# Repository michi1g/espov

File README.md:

# MiniPOV WiFi

ESP8266-Nachbau des [Adafruit MiniPOV3](https://learn.adafruit.com/minipov3) mit WiFi-Web-Editor, **2×AA-Betrieb** und optionalem **USB-C**.

## Features

- 8-LED-POV-Display (Persistence of Vision)
- **2× AA** wie beim Original (+ Boost-Wandler auf 5 V)
- **USB-C** optional auf der Platine (Laden ohne Micro-USB-Kabel am Wemos)
- WiFi **nur bei Bedarf** – FLASH-Taste, Auto-Timeout nach 3 Min.
- Web-Editor: Pixel, Text, Bild-Upload, Vorschau

## Bedienung

### POV anzeigen (Standard)

1. Einschalten (Batterie oder USB-C)
2. Gerät schwenken – gespeichertes Muster erscheint
3. WiFi ist **aus** → maximale Batterielaufzeit

### Muster ändern

1. **FLASH-Taste** am Wemos D1 Mini drücken → WiFi-AP startet
2. Mit **`MiniPOV-WiFi`** verbinden (Passwort: `minipov123`)
3. Browser: **http://192.168.4.1**
4. Muster gestalten → **An Gerät senden**
5. **WiFi beenden** (Web-UI oder FLASH-Taste) → zurück zum POV-Modus

Nach 3 Minuten ohne Aktivität schaltet WiFi automatisch ab.

## Hardware

Stückliste, Boost-Einstellung, USB-C-Platzierung: **[docs/HARDWARE.md](docs/HARDWARE.md)**

KiCad-Platinenlayout (28×118 mm, USB-C an Griffseite): **[docs/KICAD.md](docs/KICAD.md)** · Projekt in `hardware/kicad/`

Kurz:

- 2×AA → Boost 5 V → Wemos 5V-Pin
- USB-C 5 V parallel (mit Schottky-Diode)
- 8× LED + 100 Ω wie MiniPOV3

## Software flashen

[PlatformIO](https://platformio.org/) (VS Code Extension):

```bash
pio run -t upload      # Firmware
pio run -t uploadfs    # Web-Oberfläche
pio device monitor
```

Erstes Flashen bequem über **Micro-USB am Wemos** (USB-C auf Platine reicht danach für Strom).

## Konfiguration

`src/config.h`:

| Konstante | Standard | Bedeutung |
|-----------|----------|-----------|
| `WIFI_AP_TIMEOUT_MS` | 180000 | AP-Dauer (3 Min.) |
| `CPU_FREQ_POV_MHZ` | 80 | CPU im POV-Modus |
| `CONFIG_BUTTON_PIN` | 0 | FLASH-Taste |

## Projektstruktur

```
mini-pov-wifi/
├── data/           # Web-UI (LittleFS)
├── docs/           # Hardware-Doku
├── src/
│   ├── wifi_manager.*   # WiFi ein/aus, Timeout
│   ├── pov_engine.*     # LED-Timing
│   └── web_server.*     # REST + Editor
└── platformio.ini
```

## Lizenz

MIT – inspiriert vom Adafruit MiniPOV3.

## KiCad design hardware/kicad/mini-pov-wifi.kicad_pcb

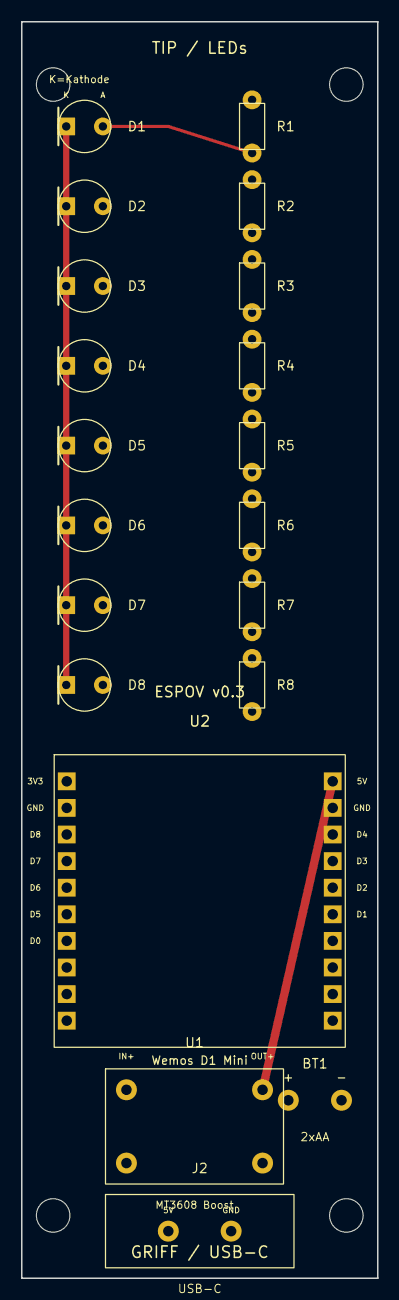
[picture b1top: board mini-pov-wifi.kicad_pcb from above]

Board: 2 copper layers, 34.0 x 120.0 mm, 24 parts (0 on the bottom side), 20 nets.

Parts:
BT1: 2xAA; Battery_2xAA
D1, D2, D3, D4, D5, D6, D7, D8: LED; LED_D5.0mm
H1, H2, H3, H4: M3; MountingHole_3.2mm
J2: USB-C; USB-C_Breakout
R1, R2, R3, R4, R5, R6, R7, R8: 100R; R_THT_1-4W
U1: MT3608 Boost; MT3608_Module
U2: Wemos D1 Mini; Wemos_D1_Mini_Socket

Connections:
+5V: J2.VBUS, U1.OUT+, U2.5V
BAT+: BT1.+, U1.IN+
BAT-: BT1.-, U1.IN-
GND: D1.K, D2.K, D3.K, D4.K, D5.K, D6.K, D7.K, D8.K, J2.GND, U1.OUT-, U2.GND1, U2.GND2
GPIO_D0: R8.1, U2.D0
GPIO_D1: R1.1, U2.D1
GPIO_D2: R2.1, U2.D2
GPIO_D4: R3.1, U2.D4
GPIO_D5: R4.1, U2.D5
GPIO_D6: R5.1, U2.D6
GPIO_D7: R6.1, U2.D7
GPIO_D8: R7.1, U2.D8
LED1: D1.A, R1.2
LED2: D2.A, R2.2
LED3: D3.A, R3.2
LED4: D4.A, R4.2
LED5: D5.A, R5.2
LED6: D6.A, R6.2
LED7: D7.A, R7.2
LED8: D8.A, R8.2
